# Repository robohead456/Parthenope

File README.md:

# Parthenope

Parthenope is a musical siren initially created for WPI's Music, Perception, and Robotics lab during the A18 practicum.

To access the original code switch to the V1 branch.

## Things being done in this version

Hardware:
- [x] Quieter motors/drivers to eliminate high pitched whine
- [x] More powerful motors to eliminate the hand spinning setup step
- [x] Motor controllers that can break to slow disk - for use in disk speed control
- [x] Change to a larger embedded board with Ethernet
- [x] More disks for a larger range
- [ ] Frame to attach all disks to
- [ ] RGB LED lights!
- [x] Better air system that can play multiple notes
- [x] Dedicated power supplies

Software:
- [ ] Multiple playing modes (single register, multi register, analog control, etc)
- [ ] Send disk speed in rps from max to the nucleo (MIDI pitch bend?)
- [x] Ethernet communication

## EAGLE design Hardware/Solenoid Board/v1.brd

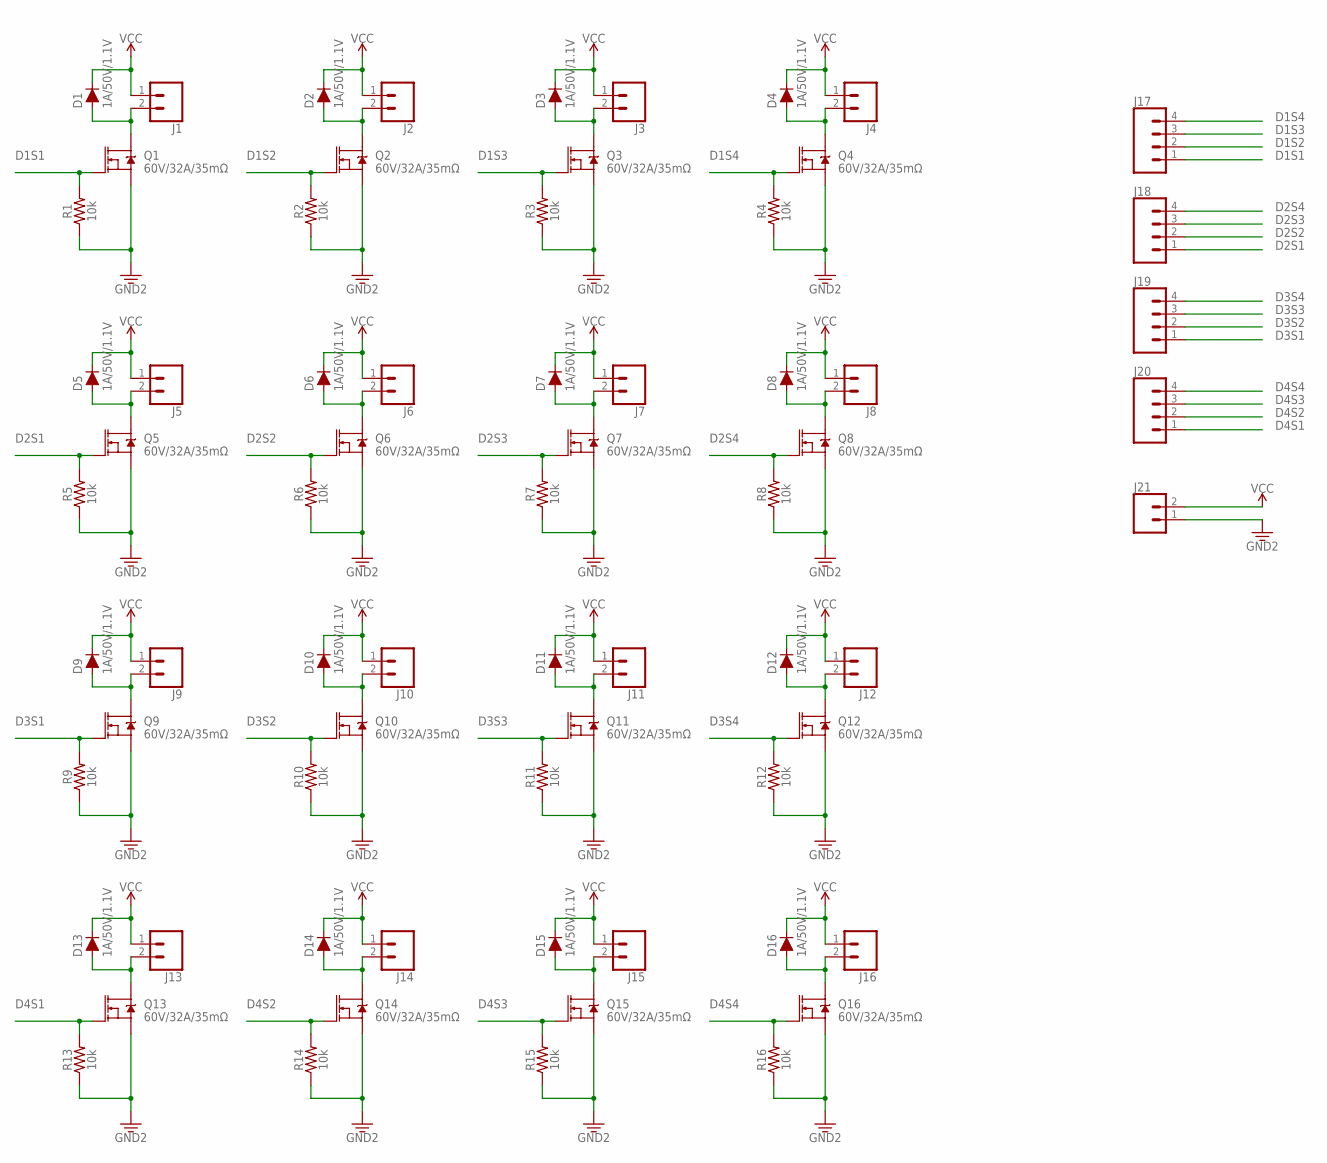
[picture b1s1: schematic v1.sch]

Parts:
D1, D2, D3, D4, D5, D6, D7, D8, D9, D10, D11, D12, D13, D14, D15, D16: 1A/50V/1.1V; DIODE-1N4001
J1, J2, J3, J4, J5, J6, J7, J8, J9, J10, J11, J12, J13, J14, J15, J16: CONN_02; 1X02
J17, J18, J19, J20: CONN_04JST-PTH-VERT; JST-4-PTH-VERT
J21: CONN_025MM; SCREWTERMINAL-5MM-2
Q1, Q2, Q3, Q4, Q5, Q6, Q7, Q8, Q9, Q10, Q11, Q12, Q13, Q14, Q15, Q16: 60V/32A/35mΩ; TO220V
R1, R2, R3, R4, R5, R6, R7, R8, R9, R10, R11, R12, R13, R14, R15, R16: 10k; AXIAL-0.3-KIT

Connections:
D1S1: J17.1, Q1.1 (G), R1.P$2 (2)
D1S2: J17.2, Q2.1 (G), R2.P$2 (2)
D1S3: J17.3, Q3.1 (G), R3.P$2 (2)
D1S4: J17.4, Q4.1 (G), R4.P$2 (2)
D2S1: J18.1, Q5.1 (G), R5.P$2 (2)
D2S2: J18.2, Q6.1 (G), R6.P$2 (2)
D2S3: J18.3, Q7.1 (G), R7.P$2 (2)
D2S4: J18.4, Q8.1 (G), R8.P$2 (2)
D3S1: J19.1, Q9.1 (G), R9.P$2 (2)
D3S2: J19.2, Q10.1 (G), R10.P$2 (2)
D3S3: J19.3, Q11.1 (G), R11.P$2 (2)
D3S4: J19.4, Q12.1 (G), R12.P$2 (2)
D4S1: J20.1, Q13.1 (G), R13.P$2 (2)
D4S2: J20.2, Q14.1 (G), R14.P$2 (2)
D4S3: J20.3, Q15.1 (G), R15.P$2 (2)
D4S4: J20.4, Q16.1 (G), R16.P$2 (2)
GND: J21.1, Q1.3 (S), Q2.3 (S), Q3.3 (S), Q4.3 (S), Q5.3 (S), Q6.3 (S), Q7.3 (S), Q8.3 (S), Q9.3 (S), Q10.3 (S), Q11.3 (S), Q12.3 (S), Q13.3 (S), Q14.3 (S), Q15.3 (S), Q16.3 (S), R1.P$1 (1), R2.P$1 (1), R3.P$1 (1), R4.P$1 (1), R5.P$1 (1), R6.P$1 (1), R7.P$1 (1), R8.P$1 (1), R9.P$1 (1), R10.P$1 (1), R11.P$1 (1), R12.P$1 (1), R13.P$1 (1), R14.P$1 (1), R15.P$1 (1), R16.P$1 (1)
unnamed: D13.A, J13.2, Q13.2 (D)
unnamed: D14.A, J14.2, Q14.2 (D)
unnamed: D1.A, J1.2, Q1.2 (D)
unnamed: D2.A, J2.2, Q2.2 (D)
unnamed: D15.A, J15.2, Q15.2 (D)
unnamed: D3.A, J3.2, Q3.2 (D)
unnamed: D16.A, J16.2, Q16.2 (D)
unnamed: D4.A, J4.2, Q4.2 (D)
unnamed: D5.A, J5.2, Q5.2 (D)
unnamed: D6.A, J6.2, Q6.2 (D)
unnamed: D7.A, J7.2, Q7.2 (D)
unnamed: D8.A, J8.2, Q8.2 (D)
unnamed: D9.A, J9.2, Q9.2 (D)
unnamed: D10.A, J10.2, Q10.2 (D)
unnamed: D11.A, J11.2, Q11.2 (D)
unnamed: D12.A, J12.2, Q12.2 (D)
VCC: D1.C, D2.C, D3.C, D4.C, D5.C, D6.C, D7.C, D8.C, D9.C, D10.C, D11.C, D12.C, D13.C, D14.C, D15.C, D16.C, J1.1, J2.1, J3.1, J4.1, J5.1, J6.1, J7.1, J8.1, J9.1, J10.1, J11.1, J12.1, J13.1, J14.1, J15.1, J16.1, J21.2

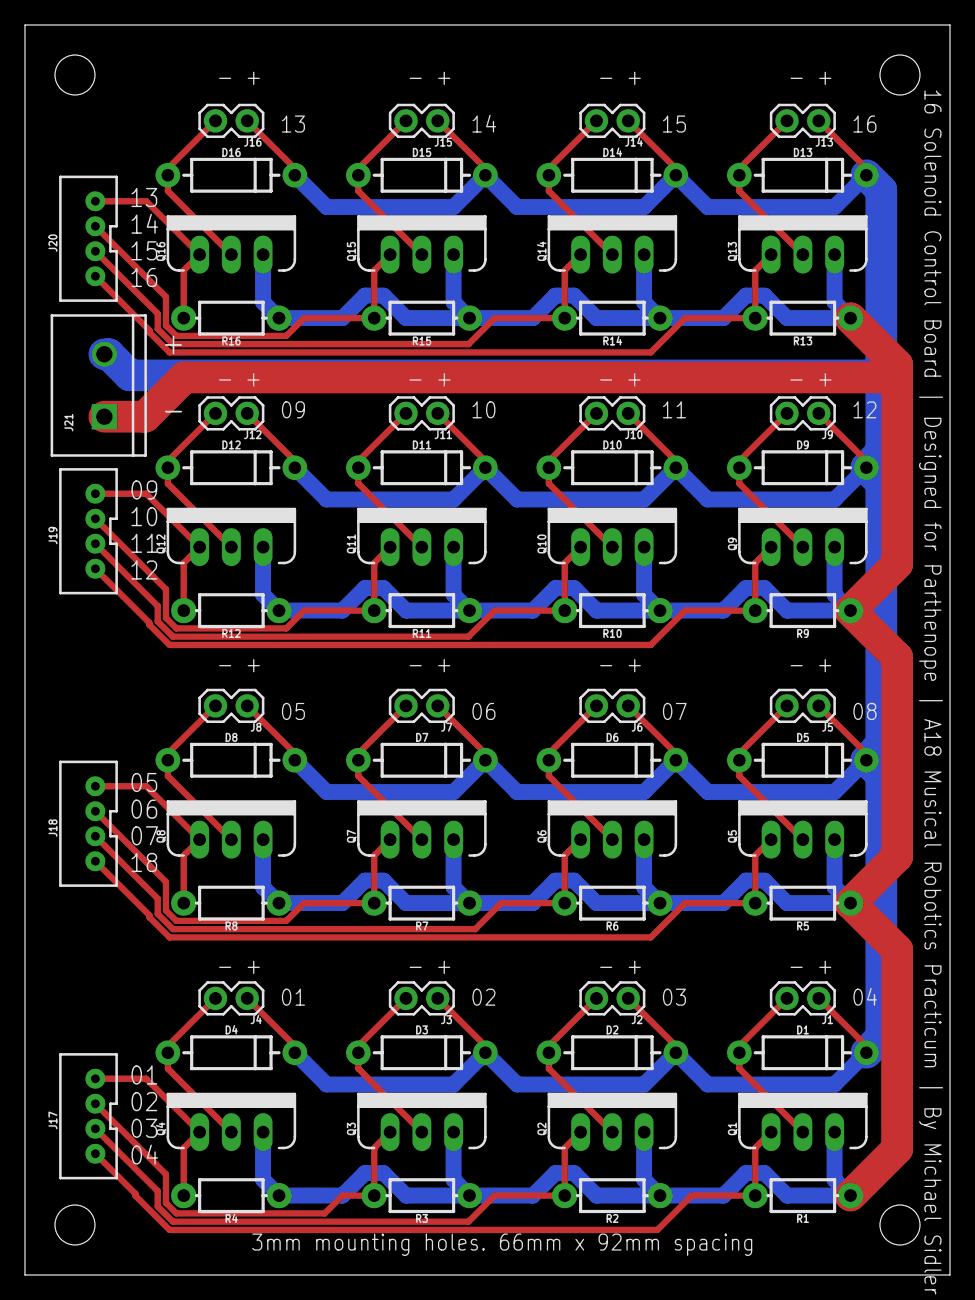
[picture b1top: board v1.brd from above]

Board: 2 copper layers, 74.0 x 100.0 mm, 69 parts (0 on the bottom side), 34 nets.

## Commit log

2018-10-13 final code from practicum
2018-10-13 Started readme
2018-10-13 added solidworks parts
2018-10-13 added solenoid board
2018-10-13 Finished user guide and future things to do
2018-10-14 Create LICENSE
2018-11-08 Update for v2
2018-11-28 nucleo code now working
2019-02-09 added new odrive test script
2019-06-17 added test script
2019-06-17 switching to PlatformIO
2019-06-21 Parthenope now uses the NSS and OSC libraries
2019-06-24 got ODrive test script working
2019-07-02 now in a state where it can play music!
2019-09-07 new main file allows for easier changing of hole numbers as well as more than 2 hole sets
2019-12-12 working on improvements
2019-12-15 updated the odrive setup script while playing with firmwares
2019-12-17 began converting from mbed/nucleo platform to arduino/samd
2019-12-19 OSC library and ethernet library are now working
2019-12-19 updated SPI speed
2019-12-20 Updated to use the GrandCentral M4 board and added ODrive communications
2019-12-20 Updated to include other constants
2019-12-20 removed old nucleo versions

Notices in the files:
parts and their libraries:
SparkFun-DiscreteSemi: Licensing: Creative Commons ShareAlike 4.0 International - https://creativecommons.org/licenses/by-sa/4.0
